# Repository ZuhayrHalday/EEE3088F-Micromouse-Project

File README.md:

# MicroMouse Project: Sensing and Power Subsystems

Welcome to the MicroMouse Project repository! The problem this entire project deals with is to design, build, and test a fully-functioning MicroMouse robot. Akin to the mice in the famous Kerplunk Experiments, a MicroMouse robot should be able to solve a maze using the shortest and fastest route possible. This README provides an overview of the project and subsystem descriptions.

## Project Overview

The goal of this project is to build key subsystems for a simplified MicroMouse, a maze-solving robot. These will be designed, manufactureed, and tested during the course of a semester.

## Subsystems

### 1. Power Subsystem (more info [here](https://github.com/ZuhayrHalday/EEE3088F-Micromouse-Project/tree/main/Power%20Subsystem))
- **Purpose:** Provide power to the entire system.
- **Key Functions:**
  - Operate two motors (each drawing up to 200mA).
  - Charge the battery from a 5V input.
  - Provide battery voltage information to the processor.
  - Include an ON/OFF switch with specific power draw requirements.
- **Connections:**
  - JST PH 2mm pin pitch connector for the battery.
  - 2x8 (2.54mm pin pitch) pin header for interfacing with the motherboard.<br />
  <br />

### 2. Sensing Subsystem (more info [here](https://github.com/ZuhayrHalday/EEE3088F-Micromouse-Project/tree/main/Sensing%20Subsystem))
- **Purpose:** Detect obstacles in the robot's path.
- **Key Functions:**
  - Detect obstacles in front and on the sides of the robot using infrared LED's and photodiodes to sense reflective obstacles.
  - Use power-saving features when not in operation.
  - Provide reliable detection data to the processor.
  - Interface with processor LEDs to indicate detected obstacles.
- **Connections:**
  - 2x14 (2.54mm pin pitch) pin header for interfacing with the motherboard.<br />
  <br />

### 3. The Motherboard
The Motherboard houses all subsystems and addresses the movement and ‘brain’ aspects of the project. The
wheels and motors of the MicroMouse are attached to the Motherboard PCB, which also mounts an STM32L476
microcontroller to manage input and output logic. Pin headers are provided for interfacing with other subsystems. This subsystem has been provided beforehand, and was not designed as a part of this project.

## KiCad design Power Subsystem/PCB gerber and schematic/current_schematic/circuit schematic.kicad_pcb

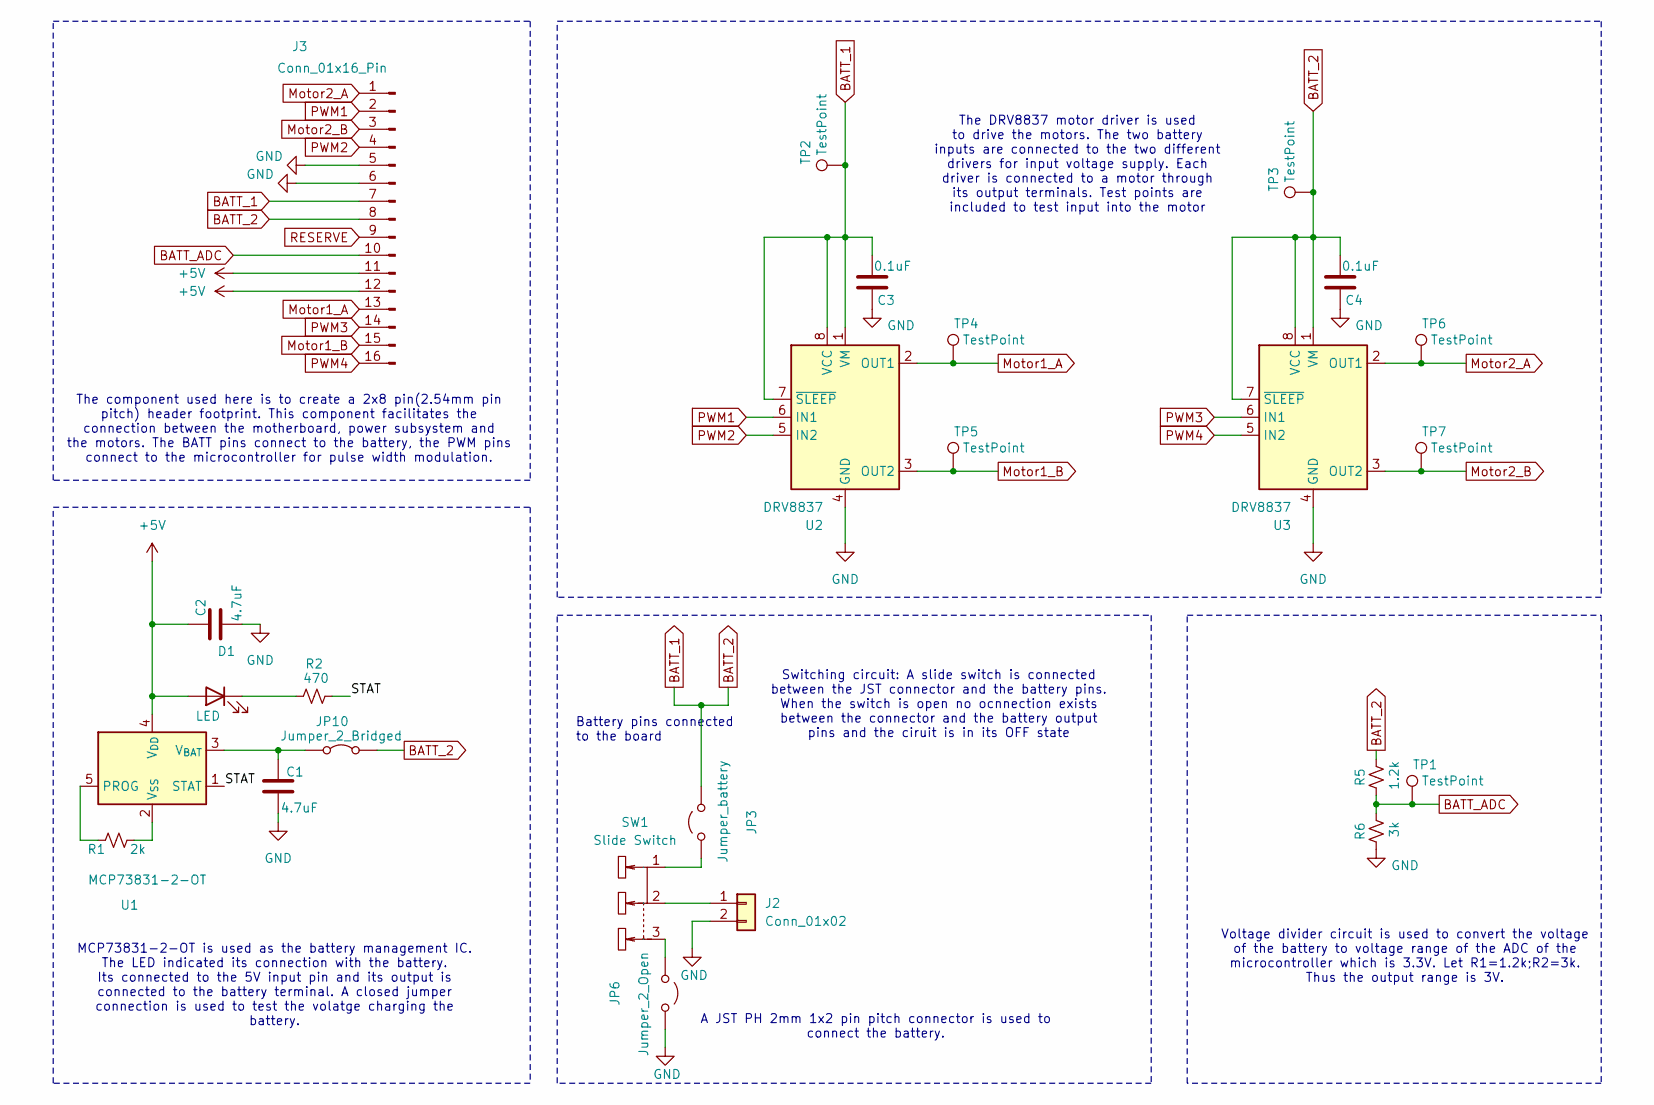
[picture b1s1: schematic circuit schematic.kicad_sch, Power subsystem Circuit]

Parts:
C1, C2: 4.7uF; C_0402_1005Metric; LCSC C1538
C3, C4: 0.1uF; C_0402_1005Metric; LCSC C1525
D1: LED; D_0603_1608Metric; LCSC C2286
J2: Conn_01x02; JST_PH_S2B-PH-K_1x02_P2.00mm_Horizontal
J3: Conn_01x16_Pin; PinHeader_2x08_P2.54mm_Vertical
JP3: Jumper_battery; SolderJumper-2_P1.3mm_Open_Pad1.0x1.5mm
JP6: Jumper_2_Open; SolderJumper-2_P1.3mm_Open_Pad1.0x1.5mm
JP10: Jumper_2_Bridged; SolderJumper-2_P1.3mm_Bridged2Bar_Pad1.0x1.5mm
R1: 2k; R_0603_1608Metric; LCSC C22975
R2: 470; R_0603_1608Metric; LCSC C23179
R5: 1.2k; R_0603_1608Metric; LCSC C22765
R6: 3k; R_0603_1608Metric; LCSC C4211
SW1: Slide Switch; SW-TH_SS-12D10L5_FOOTPRINT; LCSC C319012
TP1, TP2, TP3, TP4, TP5, TP6, TP7: TestPoint; TestPoint_Keystone_5015_Micro-Minature
U1: MCP73831-2-OT; SOT-23-5; LCSC C14879
U2, U3: DRV8837; WSON-8-1EP_2x2mm_P0.5mm_EP0.9x1.6mm; LCSC C39159

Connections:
+5V: C2.1, D1.2 (A), J3.11, J3.12, U1.4 (V_{DD})
/STAT: R2.2, U1.1 (STAT)
BATT_1: C3.2, C4.2, J3.7, J3.8, JP3.2 (B), JP10.2 (B), R5.2, TP2.1, TP3.1, U2.1 (VM), U2.7 (~SLEEP), U2.8 (VCC), U3.1 (VM), U3.7 (~SLEEP), U3.8 (VCC)
BATT_ADC: J3.10, R5.1, R6.2, TP1.1
GND: C1.2, C2.2, C3.1, C4.1, J2.2, J3.5, J3.6, JP6.2 (B), R6.1, U2.4 (GND), U2.9 (GND), U3.4 (GND), U3.9 (GND)
Motor1_A: J3.13, TP4.1, U2.2 (OUT1)
Motor1_B: J3.15, TP5.1, U2.3 (OUT2)
Motor2_A: J3.1, TP6.1, U3.2 (OUT1)
Motor2_B: J3.3, TP7.1, U3.3 (OUT2)
unnamed: D1.1 (K), R2.1
unnamed: J2.1, SW1.2
unnamed: JP3.1 (A), SW1.1
unnamed: JP6.1 (A), SW1.3
unnamed: C1.1, JP10.1 (A), U1.3 (V_{BAT})
unnamed: R1.1, U1.5 (PROG)
unnamed: R1.2, U1.2 (V_{SS})
PWM1: J3.2, U2.6 (IN1)
PWM2: J3.4, U2.5 (IN2)
PWM3: J3.14, U3.6 (IN1)
PWM4: J3.16, U3.5 (IN2)
RESERVE: J3.9

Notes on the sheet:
Switching circuit: A slide switch is connected between the JST connector and the battery pins. When the switch is open no ocnnection exists between the connector and the battery output pins and the ciruit is in its OFF state
MCP73831-2-OT is used as the battery management IC. The LED indicated its connection with the battery. Its connected to the 5V input pin and its output is connected to the battery terminal. A closed jumper connection is used to test the volatge charging the battery.
A JST PH 2mm 1x2 pin pitch connector is used to connect the battery.
Battery pins connected to the board
Voltage divider circuit is used to convert the voltage of the battery to voltage range of the ADC of the microcontroller which is 3.3V. Let R1=1.2k;R2=3k. Thus the output range is 3V.
The component used here is to create a 2x8 pin(2.54mm pin pitch) header footprint. This component facilitates the connection between the motherboard, power subsystem and the motors. The BATT pins connect to the battery, the PWM pins connect to the microcontroller for pulse width modulation.
The DRV8837 motor driver is used to drive the motors. The two battery inputs are connected to the two different drivers for input voltage supply. Each driver is connected to a motor through its output terminals. Test points are included to test input into the motor

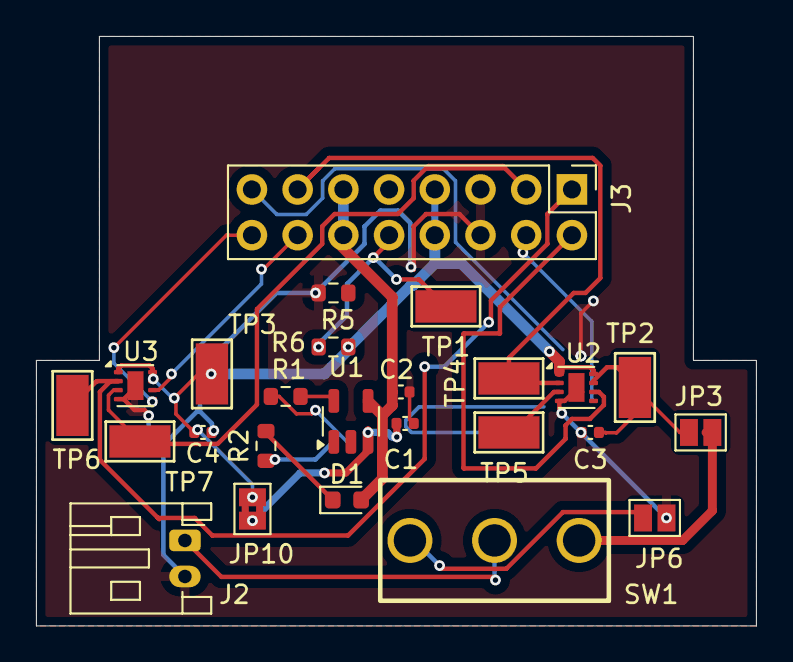
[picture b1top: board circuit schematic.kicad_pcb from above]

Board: 2 copper layers, 40.0 x 32.8 mm, 25 parts (0 on the bottom side), 20 nets.

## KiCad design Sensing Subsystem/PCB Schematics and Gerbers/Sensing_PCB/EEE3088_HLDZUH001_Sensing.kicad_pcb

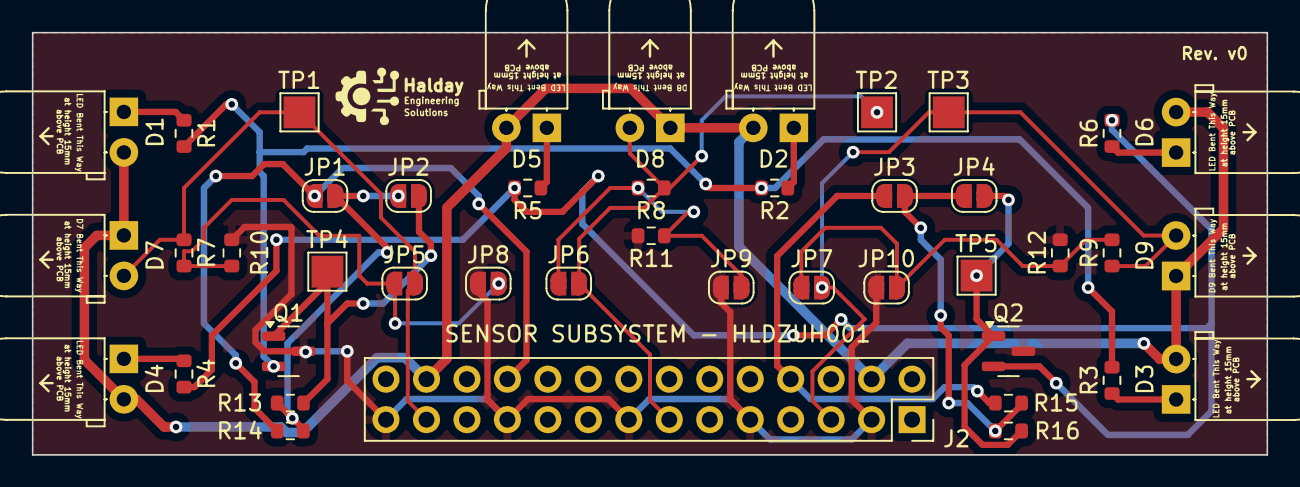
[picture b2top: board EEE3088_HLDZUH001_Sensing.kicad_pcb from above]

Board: 2 copper layers, 77.5 x 26.5 mm, 43 parts (0 on the bottom side), 22 nets.

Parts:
D1, D2, D3, D4, D5, D6: IR LED; LED_D5.0mm_Horizontal_O1.27mm_Z15.0mm
D7, D8, D9: D_Photo; LED_D5.0mm_Horizontal_O1.27mm_Z15.0mm
J2: Conn_02x14_Odd_Even; PinSocket_2x14_P2.54mm_Vertical
JP1, JP2, JP3, JP4, JP5, JP6, JP7, JP8, JP9, JP10: SolderJumper_2_Open; SolderJumper-2_P1.3mm_Open_RoundedPad1.0x1.5mm
Q1, Q2: Q_NPN_BCE; SOT-23
R1, R2, R3, R4, R5, R6: 39; R_0603_1608Metric
R7, R8, R9: 10k; R_0603_1608Metric
R10, R11, R12: 47k; R_0603_1608Metric
R13, R16: 1k; R_0603_1608Metric
R14, R15: 4.7k; R_0603_1608Metric
TP1, TP2, TP3, TP4, TP5: TestPoint; TestPoint_Pad_2.0x2.0mm

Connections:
+BATT: D1.2 (A), D2.2 (A), D3.2 (A), D4.2 (A), D5.2 (A), D6.2 (A), D7.1 (K), D8.1 (K), D9.1 (K), J2.4, J2.26
/AB0: D7.2 (A), J2.25, JP5.2 (B), R7.1, TP1.1
/PA3: D9.2 (A), J2.5, JP7.2 (B), R9.1, TP3.1
/PA6: D8.2 (A), J2.13, JP6.2 (B), R8.1, TP2.1
/PE8: J2.22, JP1.1 (A), R14.1
/PE15: J2.8, JP3.1 (A), R15.1
GND: J2.3, J2.9, J2.15, J2.21, J2.27, JP8.1 (A), JP9.1 (A), JP10.1 (A), Q1.3 (E), Q2.3 (E), R10.2, R11.2, R12.2
unnamed: D1.1 (K), R1.1
unnamed: D2.1 (K), R2.1
unnamed: D3.1 (K), R3.1
unnamed: D4.1 (K), R4.1
unnamed: D5.1 (K), R5.1
unnamed: D6.1 (K), R6.1
unnamed: JP1.2 (B), JP2.1 (A), R13.1, R14.2
unnamed: JP2.2 (B), Q1.1 (B), R13.2, TP4.1
unnamed: JP3.2 (B), JP4.1 (A), R15.2, R16.1
unnamed: JP4.2 (B), Q2.1 (B), R16.2, TP5.1
unnamed: JP5.1 (A), JP8.2 (B), R7.2, R10.1
unnamed: JP6.1 (A), JP9.2 (B), R8.2, R11.1
unnamed: JP7.1 (A), JP10.2 (B), R9.2, R12.1
unnamed: Q1.2 (C), R1.2, R2.2, R3.2
unnamed: Q2.2 (C), R4.2, R5.2, R6.2

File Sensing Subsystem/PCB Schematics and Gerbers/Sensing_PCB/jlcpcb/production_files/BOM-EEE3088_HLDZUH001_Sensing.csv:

Comment,Designator,Footprint,LCSC
1k,"R13,R16",R_0603_1608Metric,C21190
39,"R1,R2,R3,R4,R5,R6",R_0603_1608Metric,C23151
4.7k,"R14,R15",R_0603_1608Metric,C23162
10k,"R7,R8,R9",R_0603_1608Metric,C25804
47k,"R10,R11,R12",R_0603_1608Metric,C25819
D_Photo,"D7,D8,D9",LED_D5.0mm_Horizontal_O1.27mm_Z15.0mm,C2900211
IR LED,"D1,D2,D3,D4,D5,D6",LED_D5.0mm_Horizontal_O1.27mm_Z15.0mm,C55528
Q_NPN_BCE,"Q1,Q2",SOT-23,C8512

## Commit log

2024-04-24 Uploaded Sensing Subsystem folder
2024-04-24 Transistor Datasheet
2024-04-24 Resistor Datasheet (All resistors)
2024-04-24 Create information
2024-05-17 Updated README.md with images
2024-05-17 Uploaded STM32 Sensing Code for ADC and PWM
2024-07-23 Create v
